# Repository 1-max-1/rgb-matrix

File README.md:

# RGB Matrix
PCB and software for driving an 8x8 matrix of RGB LED's.

When digging through my pile of old electronics components I came across an LED matrix that I purchased many years ago. I was never able to get it working at the time, especially since I was using a breadboard and about a billion jumper cables (this matrix on a breadboard is an awful experience, would not recommend). I decided to try again now that I have acquired new skills and improved my old ones.

The software is a standard PlatformIO project, see the relevant folders for code. The PCB is a KiCAD project located in the `rgb-matrix-pcb` folder.

# Electronics

The circuit consists of four 8-bit shift registers chained together (along with some decoupling capacitors and resistors for the LED's). The shift registers are driven through SPI. The SPI lines are routed to a JST connector, so the PCB can communicate with a microcontroller. The first 3 shift registers control the cathodes of the R, G and B LED's. Each pin is assigned to one row. The final shift register is connected to the common anode of the LED's, with each pin assigned to one column. The matrix can then be driven with multiplexing by scanning through each column and briefly illuminating the desired rows. Persistence of Vision will take care of the rest.

Note: There are far better ways to implement this idea. There are more modern and efficient IC's that are designed specifically for this task. However, I wanted to do it my way and use the four 74hc595 shift registers because they are the same ones I tried to use on my original attempt. I wanted to finally get them working, just because I can.

I did not want to solder the matrix directly to the PCB (this turned out to be a lifesaving desicion later on), instead there are 2 rows of header pins. The matrix connects to these and sits on top of the PCB like a shield.

### The transistor board
I made a few mistakes. The biggest was that I completely overestimated the amount of current that the shift resgister pins could source and sink. For some reason I thought it would be enough to drive an entire row of LED's. I was wrong. Again, there are IC's like constant current shift registers that address this problem. Rather than redesign the PCB and wait for it to be manufactured again, I printed a little shelf with holes that fit 8 BJT's. I then did a little bit of hacky soldering so that the connection to the LED matrix is first routed to the transistors, which amplify the current before connecting back to the matrix.

# Software

The software is intended to be run on ESP32, it is untested for other boards. It uses hardware SPI to communicate with the matrix board. It operates by turning on each column of the matrix, one at a time. The desired rows for each column are then enabled. The LED's are then turned off and the cycle repeats with the next row. If done fast enough, the human eye will percieve the LED's as being constantly illuminated. One of the ESP32 hardware timers is used to control the cycle speed. With this method, brightness control can be achieved by not illuminating a row for some number of scan cycles.

Some display patterns have been programmed in, the current pattern can be cycled by activating the touch sensor on GPIO 13.

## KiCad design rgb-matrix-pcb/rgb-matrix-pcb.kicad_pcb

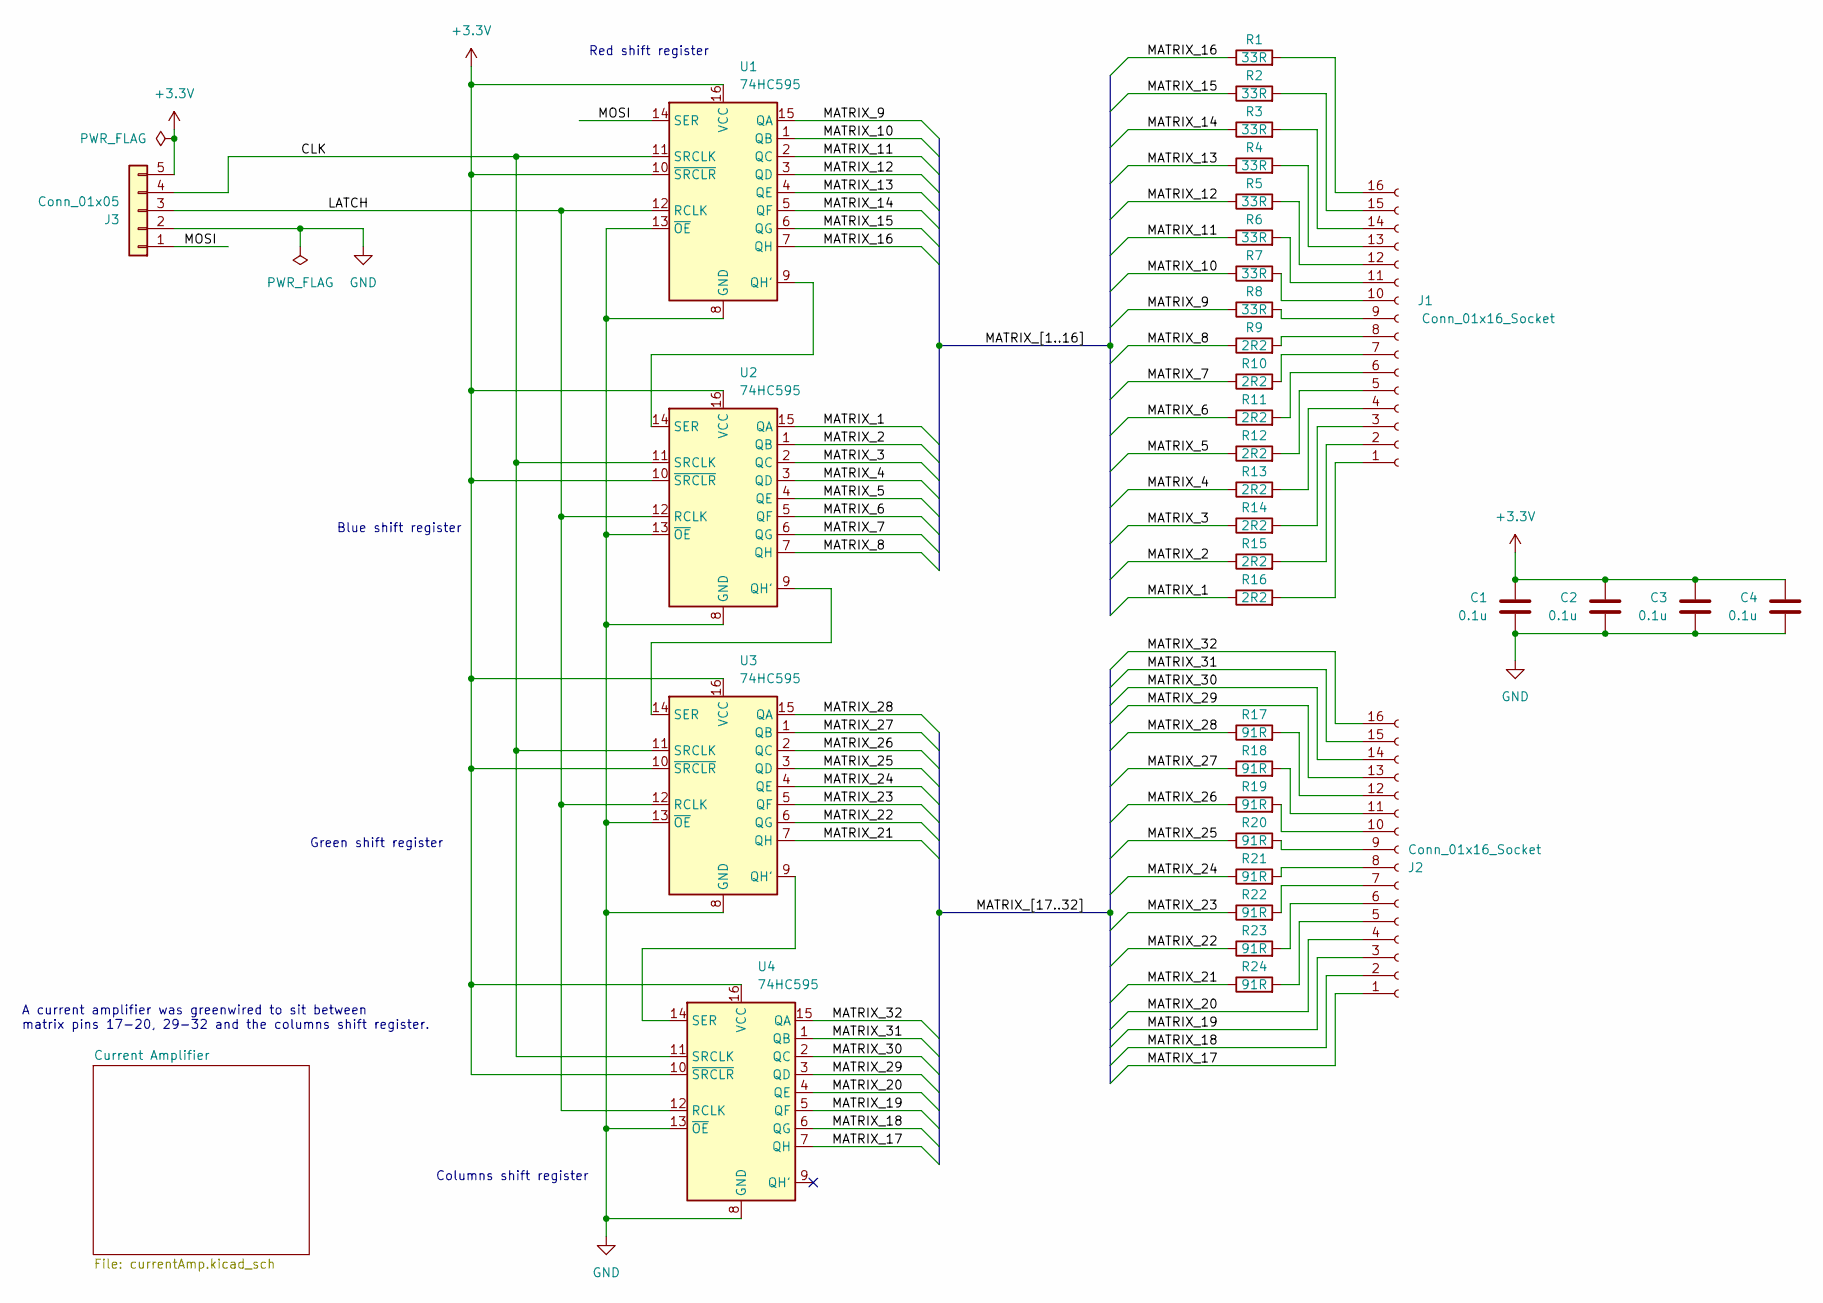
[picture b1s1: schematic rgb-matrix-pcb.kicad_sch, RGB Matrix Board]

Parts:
C1, C2, C3, C4: 0.1u; C_Disc_D3.4mm_W2.1mm_P2.50mm
J1, J2: Conn_01x16_Socket; PinSocket_1x16_P2.54mm_Vertical
J3: Conn_01x05; JST_PH_S5B-PH-K_1x05_P2.00mm_Horizontal
R1, R2, R3, R4, R5, R6, R7, R8: 33R; R_Axial_DIN0207_L6.3mm_D2.5mm_P7.62mm_Horizontal
R9, R10, R11, R12, R13, R14, R15, R16: 2R2; R_Axial_DIN0207_L6.3mm_D2.5mm_P7.62mm_Horizontal
R17, R18, R19, R20, R21, R22, R23, R24: 91R; R_Axial_DIN0207_L6.3mm_D2.5mm_P7.62mm_Horizontal
U1, U2, U3, U4: 74HC595; DIP-16_W7.62mm

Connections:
+3.3V: C1.2, C2.2, C3.2, C4.2, J3.5, U1.10 (~SRCLR), U1.16 (VCC), U2.10 (~SRCLR), U2.16 (VCC), U3.10 (~SRCLR), U3.16 (VCC), U4.10 (~SRCLR), U4.16 (VCC)
/CLK: J3.4, U1.11 (SRCLK), U2.11 (SRCLK), U3.11 (SRCLK), U4.11 (SRCLK)
/LATCH: J3.3, U1.12 (RCLK), U2.12 (RCLK), U3.12 (RCLK), U4.12 (RCLK)
/MATRIX_1: R16.1, U2.15 (QA)
/MATRIX_2: R15.1, U2.1 (QB)
/MATRIX_3: R14.1, U2.2 (QC)
/MATRIX_4: R13.1, U2.3 (QD)
/MATRIX_5: R12.1, U2.4 (QE)
/MATRIX_6: R11.1, U2.5 (QF)
/MATRIX_7: R10.1, U2.6 (QG)
/MATRIX_8: R9.1, U2.7 (QH)
/MATRIX_9: R8.1, U1.15 (QA)
/MATRIX_10: R7.1, U1.1 (QB)
/MATRIX_11: R6.1, U1.2 (QC)
/MATRIX_12: R5.1, U1.3 (QD)
/MATRIX_13: R4.1, U1.4 (QE)
/MATRIX_14: R3.1, U1.5 (QF)
/MATRIX_15: R2.1, U1.6 (QG)
/MATRIX_16: R1.1, U1.7 (QH)
/MATRIX_17: J2.1, U4.7 (QH)
/MATRIX_18: J2.2, U4.6 (QG)
/MATRIX_19: J2.3, U4.5 (QF)
/MATRIX_20: J2.4, U4.4 (QE)
/MATRIX_21: R24.1, U3.7 (QH)
/MATRIX_22: R23.1, U3.6 (QG)
/MATRIX_23: R22.1, U3.5 (QF)
/MATRIX_24: R21.1, U3.4 (QE)
/MATRIX_25: R20.1, U3.3 (QD)
/MATRIX_26: R19.1, U3.2 (QC)
/MATRIX_27: R18.1, U3.1 (QB)
/MATRIX_28: R17.1, U3.15 (QA)
/MATRIX_29: J2.13, U4.3 (QD)
/MATRIX_30: J2.14, U4.2 (QC)
/MATRIX_31: J2.15, U4.1 (QB)
/MATRIX_32: J2.16, U4.15 (QA)
/MOSI: J3.1, U1.14 (SER)
GND: C1.1, C2.1, C3.1, C4.1, J3.2, U1.8 (GND), U1.13 (~OE), U2.8 (GND), U2.13 (~OE), U3.8 (GND), U3.13 (~OE), U4.8 (GND), U4.13 (~OE)
unnamed: J1.1, R16.2
unnamed: J1.2, R15.2
unnamed: J1.3, R14.2
unnamed: J1.4, R13.2
unnamed: J1.5, R12.2
unnamed: J1.6, R11.2
unnamed: J1.7, R10.2
unnamed: J1.8, R9.2
unnamed: J1.9, R8.2
unnamed: J1.10, R7.2
unnamed: J1.11, R6.2
unnamed: J1.12, R5.2
unnamed: J1.13, R4.2
unnamed: J1.14, R3.2
unnamed: J1.15, R2.2
unnamed: J1.16, R1.2
unnamed: J2.5, R24.2
unnamed: J2.6, R23.2
unnamed: J2.7, R22.2
unnamed: J2.8, R21.2
unnamed: J2.9, R20.2
unnamed: J2.10, R19.2
unnamed: J2.11, R18.2
unnamed: J2.12, R17.2
unnamed: U1.9 (QH'), U2.14 (SER)
unnamed: U2.9 (QH'), U3.14 (SER)
unnamed: U3.9 (QH'), U4.14 (SER)

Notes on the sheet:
Green shift register
A current amplifier was greenwired to sit between matrix pins 17-20, 29-32 and the columns shift register.
Columns shift register
Blue shift register
Red shift register

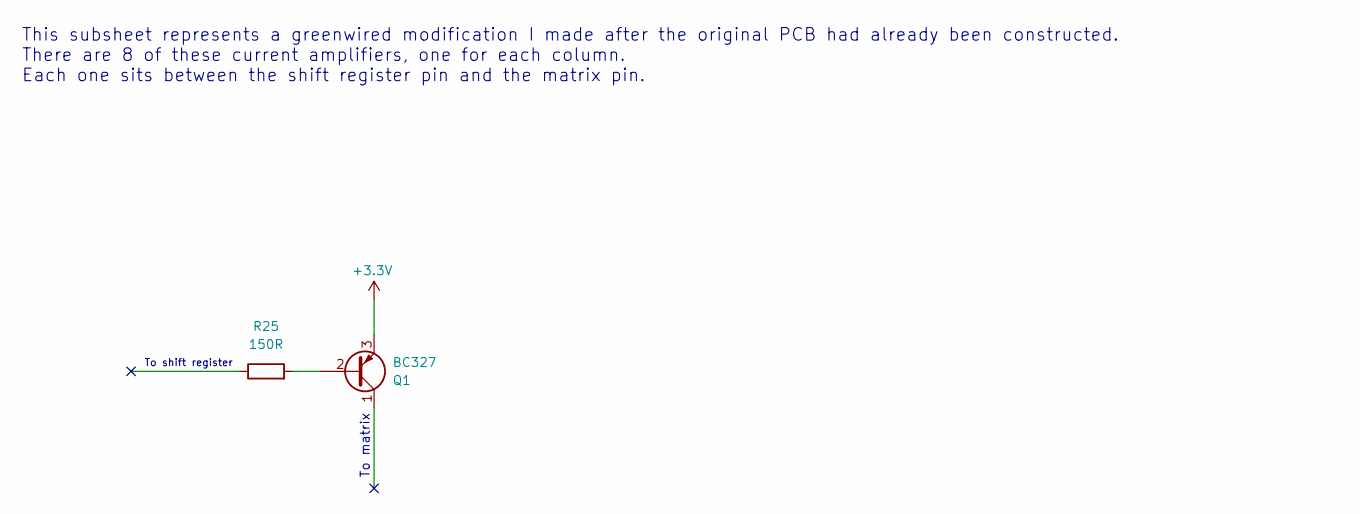
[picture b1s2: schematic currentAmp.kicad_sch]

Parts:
Q1: BC327; TO-92_Inline
R25: 150R

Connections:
unnamed: Q1.2 (B), R25.2

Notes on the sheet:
To matrix
This subsheet represents a greenwired modification I made after the original PCB had already been constructed. There are 8 of these current amplifiers, one for each column. Each one sits between the shift register pin and the matrix pin.
To shift register

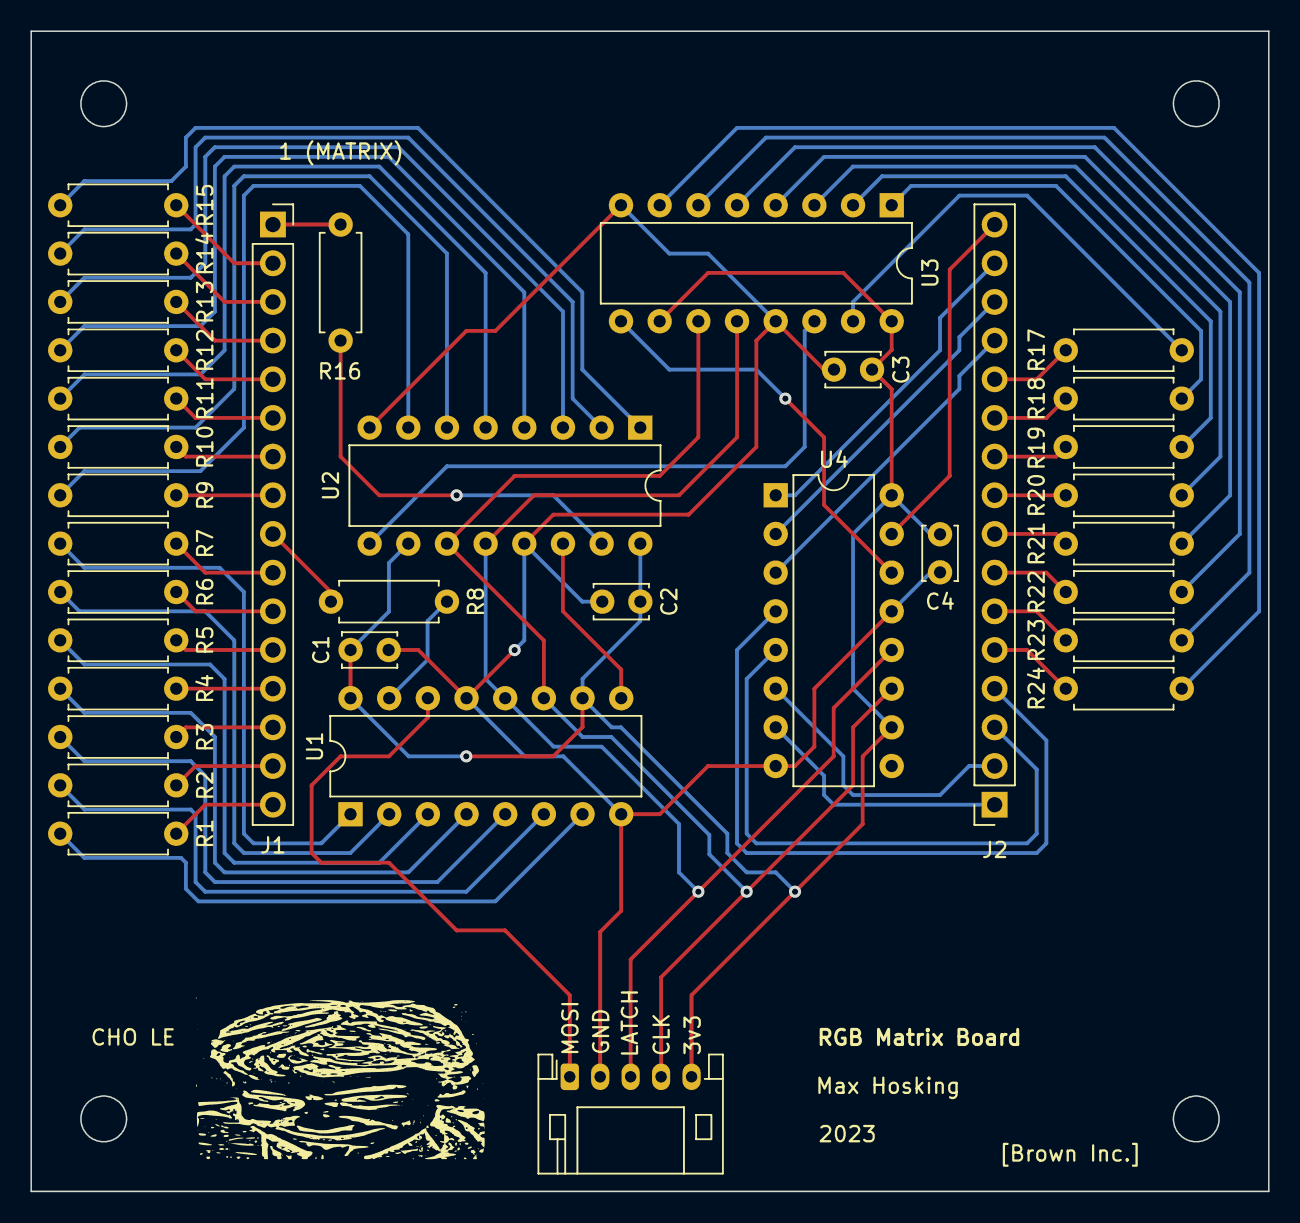
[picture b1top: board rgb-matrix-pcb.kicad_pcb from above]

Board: 2 copper layers, 81.3 x 76.2 mm, 35 parts (0 on the bottom side), 64 nets.

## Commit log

2024-07-05 Code cleanup and comments
2024-07-05 SPI chip select now controlled by hardware
2024-11-27 Partial fix for ghosting. Slight ghosting can still ocurr but barely noticeable.
2024-11-27 Updated to kicad 8.0
2024-11-29 Added basic RGB gamma correction
2024-11-29 Added ability to set pixel color in HSL format
2024-11-29 Removed testing code
2024-11-29 Updated resistor values in schematic
2024-11-30 Added schematic notes for greenwired current amplifiers
2024-12-01 Added ability to clear all pixels to off
2024-12-03 Coded some display patterns
2024-12-04 Added touch control to cycle through patterns
2025-01-04 Remove unused include
